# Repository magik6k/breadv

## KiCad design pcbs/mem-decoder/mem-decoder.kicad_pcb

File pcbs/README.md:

## BreadV PCBs

---------
| PCB           | Description                | Status        | Image                          |
|---------------|----------------------------|---------------|--------------------------------|
| ALU           | RiscV ALU                  | Scratch       |                                |
| CSR           | CSR controller             | Scratch       |                                |
| Reg           | 32bit register             | Scratch       |                                |
| ucode breaker | ucode eeprom breakout      | Scratch       |                                |
| Power         | Voltage regulator breakout | Done / In-use |                                |
| 8view         | 8bit bus bin/hex viewer    | Done / In-use |  |
| 8view-out     | 8view ffc breakout         | Done / In-use |                                |

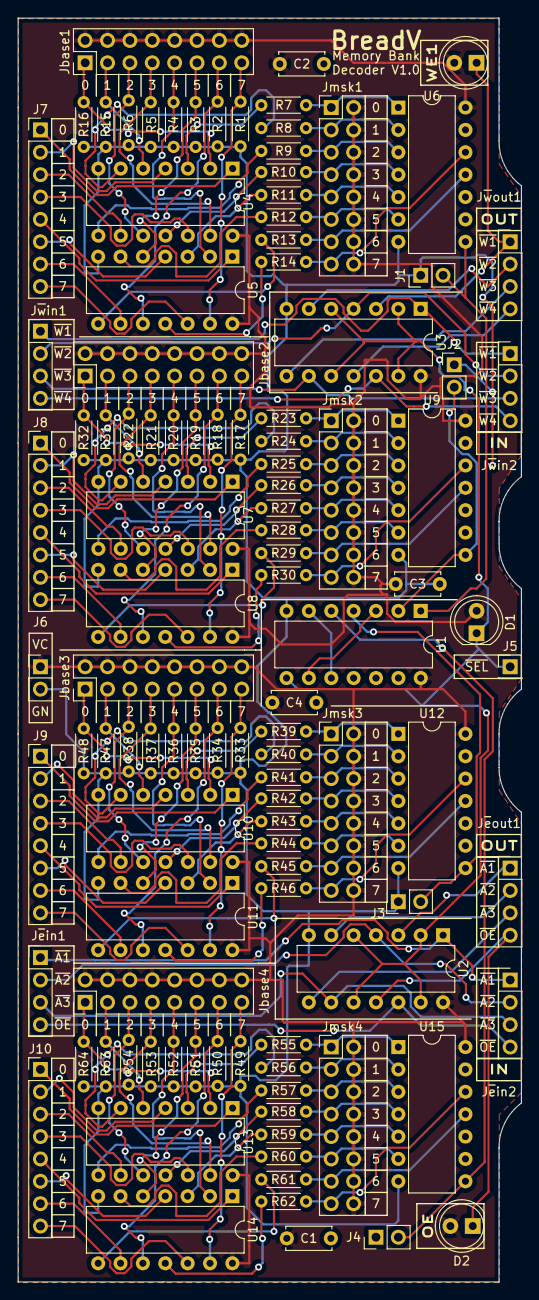
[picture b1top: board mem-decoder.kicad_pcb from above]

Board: 2 copper layers, 57.1 x 143.5 mm, 110 parts (0 on the bottom side), 153 nets.

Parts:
C1, C2, C3, C4: C; C_Disc_D5.0mm_W2.5mm_P5.00mm
D1, D2, D3: LED; LED_D5.0mm
J1, J2, J3, J4, J6: Conn_01x02_Male; PinHeader_1x02_P2.54mm_Vertical
J5: Conn_01x01_Male; PinHeader_1x01_P2.54mm_Vertical
J7, J8, J9, J10: Conn_01x08_Female; PinHeader_1x08_P2.54mm_Vertical
Jbase1, Jbase2, Jbase3, Jbase4: Conn_02x08_Odd_Even; PinHeader_2x08_P2.54mm_Vertical
Jmsk1, Jmsk2, Jmsk3, Jmsk4: Conn_02x08_Odd_Even; PinHeader_2x08_P2.54mm_Vertical
J~{e}in1, J~{e}in2: Conn_01x04_Male; PinHeader_1x04_P2.54mm_Vertical
J~{e}out1: Conn_01x04_Male; PinHeader_1x04_P2.54mm_Vertical
J~{w}in1, J~{w}in2: Conn_01x04_Male; PinHeader_1x04_P2.54mm_Vertical
J~{w}out1: Conn_01x04_Male; PinHeader_1x04_P2.54mm_Vertical
R1, R2, R3, R4, R5, R6, R7, R8, R9, R10, R11, R12, R13, R14, R15, R16, R17, R18, R19, R20, R21, R22, R23, R24, R25, R26, R27, R28, R29, R30, R31, R32, R33, R34, R35, R36, R37, R38, R39, R40, R41, R42, R43, R44, R45, R46, R47, R48, R49, R50, R51, R52, R53, R54, R55, R56, R57, R58, R59, R60, R61, R62, R63, R64: 1K; R_Axial_DIN0204_L3.6mm_D1.6mm_P5.08mm_Horizontal
U1, U2, U3: 74LS32; DIP-14_W7.62mm
U4, U5, U7, U8, U10, U11, U13, U14: 74LS08; DIP-14_W7.62mm
U6, U9, U12, U15: 74LS30; DIP-14_W7.62mm

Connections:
+5V: C1.1, C2.1, C3.1, C4.1, D1.2 (A), D2.2 (A), D3.2 (A), J6.1, Jbase1.2, Jbase1.4, Jbase1.6, Jbase1.8, Jbase1.10, Jbase1.12, Jbase1.14, Jbase1.16, Jbase2.2, Jbase2.4, Jbase2.6, Jbase2.8, Jbase2.10, Jbase2.12, Jbase2.14, Jbase2.16, Jbase3.2, Jbase3.4, Jbase3.6, Jbase3.8, Jbase3.10, Jbase3.12, Jbase3.14, Jbase3.16, Jbase4.2, Jbase4.4, Jbase4.6, Jbase4.8, Jbase4.10, Jbase4.12, Jbase4.14, Jbase4.16, Jmsk1.2, Jmsk1.4, Jmsk1.6, Jmsk1.8, Jmsk1.10, Jmsk1.12, Jmsk1.14, Jmsk1.16, Jmsk2.2, Jmsk2.4, Jmsk2.6, Jmsk2.8, Jmsk2.10, Jmsk2.12, Jmsk2.14, Jmsk2.16, Jmsk3.2, Jmsk3.4, Jmsk3.6, Jmsk3.8, Jmsk3.10, Jmsk3.12, Jmsk3.14, Jmsk3.16, Jmsk4.2, Jmsk4.4, Jmsk4.6, Jmsk4.8, Jmsk4.10, Jmsk4.12, Jmsk4.14, Jmsk4.16, U1.14 (VCC), U2.14 (VCC), U3.14 (VCC), U4.14 (VCC), U5.14 (VCC), U6.14 (VCC), U7.14 (VCC), U8.14 (VCC), U9.14 (VCC), U10.14 (VCC), U11.14 (VCC), U12.14 (VCC), U13.14 (VCC), U14.14 (VCC), U15.14 (VCC)
/8bitmask1/A1: J8.1, U7.1
/8bitmask1/A2: J8.2, U7.4
/8bitmask1/A3: J8.3, U7.9
/8bitmask1/A4: J8.4, U7.12
/8bitmask1/A5: J8.5, U8.1
/8bitmask1/A6: J8.6, U8.4
/8bitmask1/A7: J8.7, U8.9
/8bitmask1/A8: J8.8, U8.12
/8bitmask1/B1: Jbase2.1, R32.2, U7.2
/8bitmask1/B2: Jbase2.3, R31.2, U7.5
/8bitmask1/B3: Jbase2.5, R22.2, U7.10
/8bitmask1/B4: Jbase2.7, R21.2, U7.13
/8bitmask1/B5: Jbase2.9, R20.2, U8.2
/8bitmask1/B6: Jbase2.11, R19.2, U8.5
/8bitmask1/B7: Jbase2.13, R18.2, U8.10
/8bitmask1/B8: Jbase2.15, R17.2, U8.13
/8bitmask1/M1: Jmsk2.1, R23.2, U9.1
/8bitmask1/M2: Jmsk2.3, R24.2, U9.2
/8bitmask1/M3: Jmsk2.5, R25.2, U9.3
/8bitmask1/M4: Jmsk2.7, R26.2, U9.4
/8bitmask1/M5: Jmsk2.9, R27.2, U9.5
/8bitmask1/M6: Jmsk2.11, R28.2, U9.6
/8bitmask1/M7: Jmsk2.13, R29.2, U9.11
/8bitmask1/M8: Jmsk2.15, R30.2, U9.12
/8bitmask1/O: J2.2, U1.2, U9.8
/8bitmask2/A1: J9.1, U10.1
/8bitmask2/A2: J9.2, U10.4
/8bitmask2/A3: J9.3, U10.9
/8bitmask2/A4: J9.4, U10.12
/8bitmask2/A5: J9.5, U11.1
/8bitmask2/A6: J9.6, U11.4
/8bitmask2/A7: J9.7, U11.9
/8bitmask2/A8: J9.8, U11.12
/8bitmask2/B1: Jbase3.1, R48.2, U10.2
/8bitmask2/B2: Jbase3.3, R47.2, U10.5
/8bitmask2/B3: Jbase3.5, R38.2, U10.10
/8bitmask2/B4: Jbase3.7, R37.2, U10.13
/8bitmask2/B5: Jbase3.9, R36.2, U11.2
/8bitmask2/B6: Jbase3.11, R35.2, U11.5
/8bitmask2/B7: Jbase3.13, R34.2, U11.10
/8bitmask2/B8: Jbase3.15, R33.2, U11.13
/8bitmask2/M1: Jmsk3.1, R39.2, U12.1
/8bitmask2/M2: Jmsk3.3, R40.2, U12.2
/8bitmask2/M3: Jmsk3.5, R41.2, U12.3
/8bitmask2/M4: Jmsk3.7, R42.2, U12.4
/8bitmask2/M5: Jmsk3.9, R43.2, U12.5
/8bitmask2/M6: Jmsk3.11, R44.2, U12.6
/8bitmask2/M7: Jmsk3.13, R45.2, U12.11
/8bitmask2/M8: Jmsk3.15, R46.2, U12.12
/8bitmask2/O: J3.2, U1.4, U12.8
/8bitmask3/A1: J10.1, U13.1
/8bitmask3/A2: J10.2, U13.4
/8bitmask3/A3: J10.3, U13.9
/8bitmask3/A4: J10.4, U13.12
/8bitmask3/A5: J10.5, U14.1
/8bitmask3/A6: J10.6, U14.4
/8bitmask3/A7: J10.7, U14.9
/8bitmask3/A8: J10.8, U14.12
/8bitmask3/B1: Jbase4.1, R64.2, U13.2
/8bitmask3/B2: Jbase4.3, R63.2, U13.5
/8bitmask3/B3: Jbase4.5, R54.2, U13.10
/8bitmask3/B4: Jbase4.7, R53.2, U13.13
/8bitmask3/B5: Jbase4.9, R52.2, U14.2
/8bitmask3/B6: Jbase4.11, R51.2, U14.5
/8bitmask3/B7: Jbase4.13, R50.2, U14.10
/8bitmask3/B8: Jbase4.15, R49.2, U14.13
/8bitmask3/M1: Jmsk4.1, R55.2, U15.1
/8bitmask3/M2: Jmsk4.3, R56.2, U15.2
/8bitmask3/M3: Jmsk4.5, R57.2, U15.3
/8bitmask3/M4: Jmsk4.7, R58.2, U15.4
/8bitmask3/M5: Jmsk4.9, R59.2, U15.5
/8bitmask3/M6: Jmsk4.11, R60.2, U15.6
/8bitmask3/M7: Jmsk4.13, R61.2, U15.11
/8bitmask3/M8: Jmsk4.15, R62.2, U15.12
/8bitmask3/O: J4.2, U1.5, U15.8
/8bitmask/A1: J7.1, U4.1
/8bitmask/A2: J7.2, U4.4
/8bitmask/A3: J7.3, U4.9
/8bitmask/A4: J7.4, U4.12
/8bitmask/A5: J7.5, U5.1
/8bitmask/A6: J7.6, U5.4
/8bitmask/A7: J7.7, U5.9
/8bitmask/A8: J7.8, U5.12
/8bitmask/B1: Jbase1.1, R16.2, U4.2
/8bitmask/B2: Jbase1.3, R15.2, U4.5
/8bitmask/B3: Jbase1.5, R6.2, U4.10
/8bitmask/B4: Jbase1.7, R5.2, U4.13
/8bitmask/B5: Jbase1.9, R4.2, U5.2
/8bitmask/B6: Jbase1.11, R3.2, U5.5
/8bitmask/B7: Jbase1.13, R2.2, U5.10
/8bitmask/B8: Jbase1.15, R1.2, U5.13
/8bitmask/M1: Jmsk1.1, R7.2, U6.1
/8bitmask/M2: Jmsk1.3, R8.2, U6.2
/8bitmask/M3: Jmsk1.5, R9.2, U6.3
/8bitmask/M4: Jmsk1.7, R10.2, U6.4
/8bitmask/M5: Jmsk1.9, R11.2, U6.5
/8bitmask/M6: Jmsk1.11, R12.2, U6.6
/8bitmask/M7: Jmsk1.13, R13.2, U6.11
/8bitmask/M8: Jmsk1.15, R14.2, U6.12
/8bitmask/O: J1.2, U1.1, U6.8
/~sel: D1.1 (K), J5.1, U1.8, U2.2, U2.5, U2.10, U2.13, U3.2, U3.5, U3.10, U3.13
GND: C1.2, C2.2, C3.2, C4.2, J1.1, J2.1, J3.1, J4.1, J6.2, R1.1, R2.1, R3.1, R4.1, R5.1, R6.1, R15.1, R16.1, R17.1, R18.1, R19.1, R20.1, R21.1, R22.1, R31.1, R32.1, R33.1, R34.1, R35.1, R36.1, R37.1, R38.1, R47.1, R48.1, R49.1, R50.1, R51.1, R52.1, R53.1, R54.1, R63.1, R64.1, U1.7 (GND), U2.7 (GND), U3.7 (GND), U4.7 (GND), U5.7 (GND), U6.7 (GND), U7.7 (GND), U8.7 (GND), U9.7 (GND), U10.7 (GND), U11.7 (GND), U12.7 (GND), U13.7 (GND), U14.7 (GND), U15.7 (GND)
unnamed: R7.1, U4.3
unnamed: R8.1, U4.6
unnamed: R9.1, U4.8
unnamed: R10.1, U4.11
unnamed: R11.1, U5.3
unnamed: R12.1, U5.6
unnamed: R13.1, U5.8
unnamed: R14.1, U5.11
unnamed: R23.1, U7.3
unnamed: R24.1, U7.6
unnamed: R25.1, U7.8
unnamed: R26.1, U7.11
unnamed: R27.1, U8.3
unnamed: R28.1, U8.6
unnamed: R29.1, U8.8
unnamed: R30.1, U8.11
unnamed: R39.1, U10.3
unnamed: R40.1, U10.6
unnamed: R41.1, U10.8
unnamed: R42.1, U10.11
unnamed: R43.1, U11.3
unnamed: R44.1, U11.6
unnamed: R45.1, U11.8
unnamed: R46.1, U11.11
unnamed: R55.1, U13.3
unnamed: R56.1, U13.6
unnamed: R57.1, U13.8
unnamed: R58.1, U13.11
unnamed: R59.1, U14.3
unnamed: R60.1, U14.6
unnamed: R61.1, U14.8
unnamed: R62.1, U14.11
unnamed: U1.3, U1.9
unnamed: U1.6, U1.10
~Laux1o: J~{e}out1.1, U2.3
~Laux1: J~{e}in1.1, J~{e}in2.1, U2.1
~Laux2o: J~{e}out1.2, U2.6
~Laux2: J~{e}in1.2, J~{e}in2.2, U2.4
~Laux3o: J~{e}out1.3, U2.8
~Laux3: J~{e}in1.3, J~{e}in2.3, U2.9
~OEin: J~{e}in1.4, J~{e}in2.4, U2.12
~OEout: D2.1 (K), J~{e}out1.4, U2.11
~WEin1: J~{w}in1.1, J~{w}in2.1, U3.1
~WEin2: J~{w}in1.2, J~{w}in2.2, U3.4
~WEin3: J~{w}in1.3, J~{w}in2.3, U3.9
~WEin4: J~{w}in1.4, J~{w}in2.4, U3.12
~WEout1: D3.1 (K), J~{w}out1.1, U3.3
~WEout2: J~{w}out1.2, U3.6
~WEout3: J~{w}out1.3, U3.8
~WEout4: J~{w}out1.4, U3.11

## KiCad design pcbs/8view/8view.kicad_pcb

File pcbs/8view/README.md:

## 8view

8bit bus bin/hex viewer

### Features
* 8 LEDs viewing bits
* 2 7-segment displays for hex driven by attiny828 used mostly as LUT

### Flashing

```
$ avr-gcc -mmcu=attiny828 8view.c -Os -o 8view.o && avr-objcopy -j .text -j .data -O ihex 8view.o 8view.hex

# Works with arduino isp
$ avrdude -p t828 -P /dev/ttyXX -c avrisp -b 19200 -U flash:w:8view.hex -F
```

### TODO
* Make high-impedance
* Implement snapshot / record mode

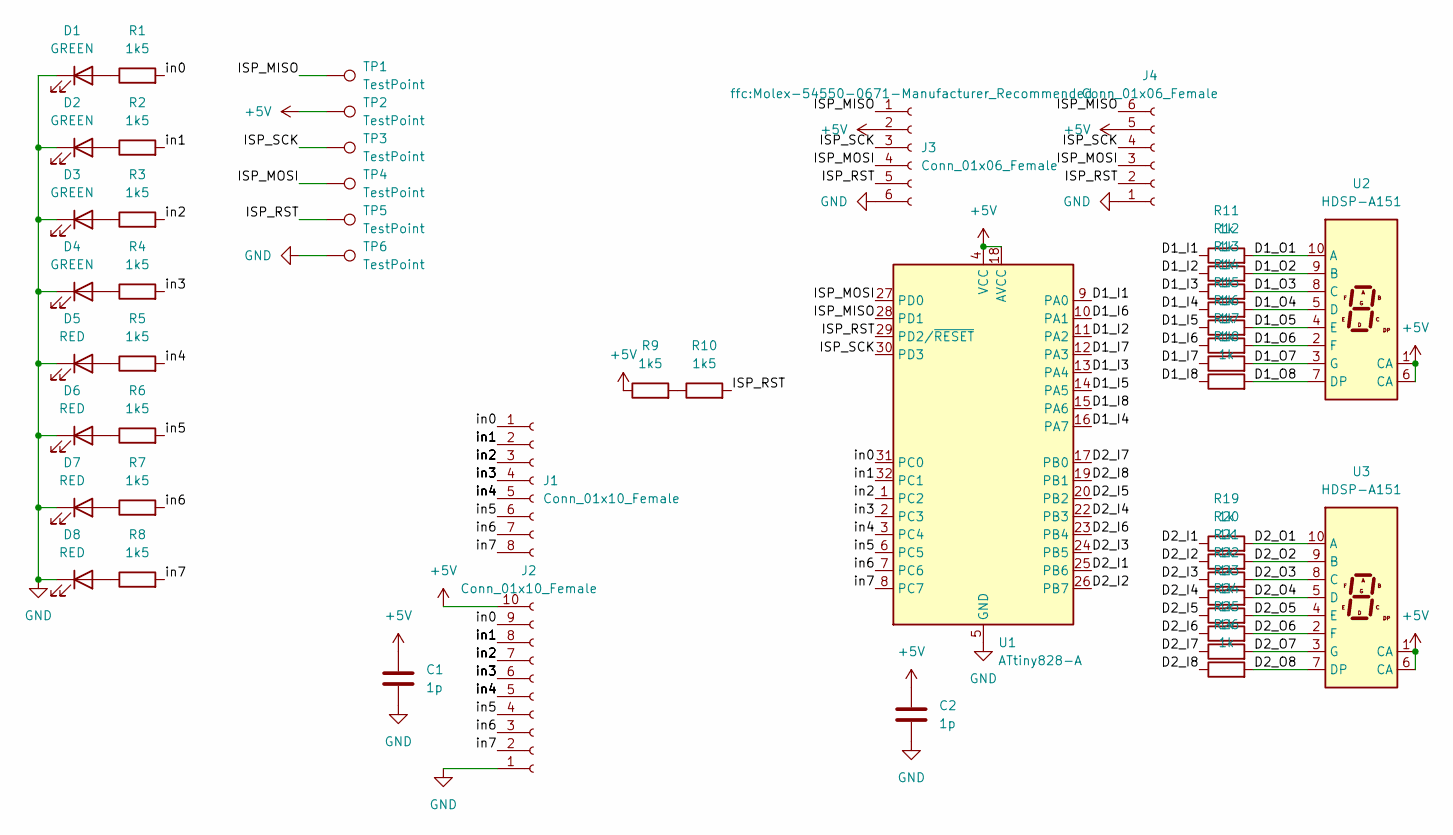
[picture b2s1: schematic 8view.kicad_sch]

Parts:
C1, C2: 1p; C_0603_1608Metric
D1, D2, D3, D4: GREEN; LED_0603_1608Metric
D5, D6, D7, D8: RED; LED_0603_1608Metric
J1: Conn_01x10_Female; PinHeader_1x08_P2.54mm_Horizontal
J2: Conn_01x10_Female; PinHeader_1x10_P2.54mm_Horizontal
J3, J4: Conn_01x06_Female; Molex-54550-0671-Manufacturer_Recommended
R1, R2, R3, R4, R5, R6, R7, R8, R9, R10: 1k5; R_0402_1005Metric
R11, R12, R13, R14, R15, R16, R17, R18, R19, R20, R21, R22, R23, R24, R25, R26: 1k; R_0402_1005Metric
TP1, TP2, TP3, TP4, TP5, TP6: TestPoint; TestPoint_Pad_D1.5mm
U1: ATtiny828-A; TQFP-32_7x7mm_P0.8mm
U2, U3: HDSP-A151

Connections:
+5V: C1.1, C2.1, J2.10, J3.2, J4.5, R9.1, TP2.1, U1.4 (VCC), U1.18 (AVCC), U2.1 (CA), U2.6 (CA), U3.1 (CA), U3.6 (CA)
/D1_I1: R11.1, U1.9 (PA0)
/D1_I2: R12.1, U1.11 (PA2)
/D1_I3: R13.1, U1.13 (PA4)
/D1_I4: R14.1, U1.16 (PA7)
/D1_I5: R15.1, U1.14 (PA5)
/D1_I6: R16.1, U1.10 (PA1)
/D1_I7: R17.1, U1.12 (PA3)
/D1_I8: R18.1, U1.15 (PA6)
/D1_O1: R11.2, U2.10 (A)
/D1_O2: R12.2, U2.9 (B)
/D1_O3: R13.2, U2.8 (C)
/D1_O4: R14.2, U2.5 (D)
/D1_O5: R15.2, U2.4 (E)
/D1_O6: R16.2, U2.2 (F)
/D1_O7: R17.2, U2.3 (G)
/D1_O8: R18.2, U2.7 (DP)
/D2_I1: R19.1, U1.25 (PB6)
/D2_I2: R20.1, U1.26 (PB7)
/D2_I3: R21.1, U1.24 (PB5)
/D2_I4: R22.1, U1.22 (PB3)
/D2_I5: R23.1, U1.20 (PB2)
/D2_I6: R24.1, U1.23 (PB4)
/D2_I7: R25.1, U1.17 (PB0)
/D2_I8: R26.1, U1.19 (PB1)
/D2_O1: R19.2, U3.10 (A)
/D2_O2: R20.2, U3.9 (B)
/D2_O3: R21.2, U3.8 (C)
/D2_O4: R22.2, U3.5 (D)
/D2_O5: R23.2, U3.4 (E)
/D2_O6: R24.2, U3.2 (F)
/D2_O7: R25.2, U3.3 (G)
/D2_O8: R26.2, U3.7 (DP)
/ISP_MISO: J3.1, J4.6, TP1.1, U1.28 (PD1)
/ISP_MOSI: J3.4, J4.3, TP4.1, U1.27 (PD0)
/ISP_RST: J3.5, J4.2, R10.2, TP5.1, U1.29 (PD2/~RESET)
/ISP_SCK: J3.3, J4.4, TP3.1, U1.30 (PD3)
/in0: J1.1, J2.9, R1.2, U1.31 (PC0)
/in1: J1.2, J2.8, R2.2, U1.32 (PC1)
/in2: J1.3, J2.7, R3.2, U1.1 (PC2)
/in3: J1.4, J2.6, R4.2, U1.2 (PC3)
/in4: J1.5, J2.5, R5.2, U1.3 (PC4)
/in5: J1.6, J2.4, R6.2, U1.6 (PC5)
/in6: J1.7, J2.3, R7.2, U1.7 (PC6)
/in7: J1.8, J2.2, R8.2, U1.8 (PC7)
GND: C1.2, C2.2, D1.1 (K), D2.1 (K), D3.1 (K), D4.1 (K), D5.1 (K), D6.1 (K), D7.1 (K), D8.1 (K), J2.1, J3.6, J4.1, TP6.1, U1.5 (GND), U1.21 (GND)
unnamed: D1.2 (A), R1.1
unnamed: D2.2 (A), R2.1
unnamed: D3.2 (A), R3.1
unnamed: D4.2 (A), R4.1
unnamed: D5.2 (A), R5.1
unnamed: D6.2 (A), R6.1
unnamed: D7.2 (A), R7.1
unnamed: D8.2 (A), R8.1
unnamed: R9.2, R10.1

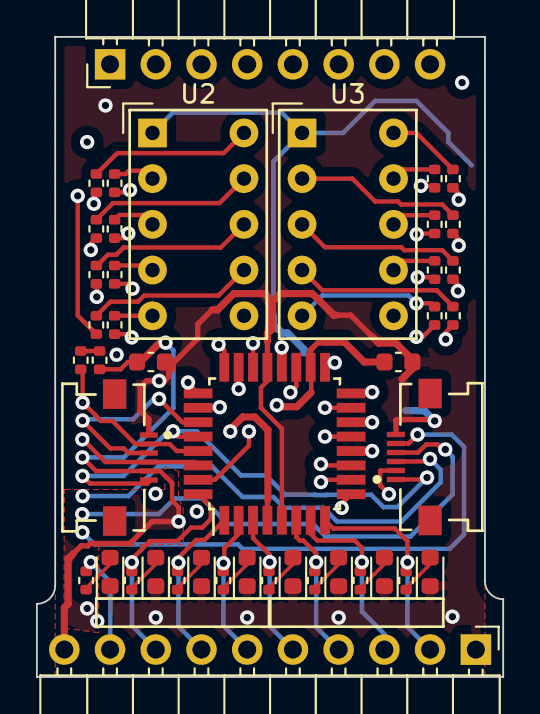
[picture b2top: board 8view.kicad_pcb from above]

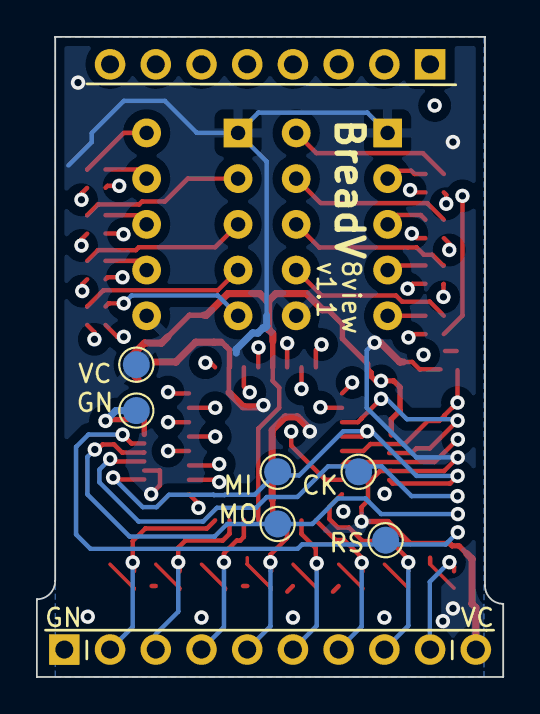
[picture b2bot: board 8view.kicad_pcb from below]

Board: 4 copper layers, 25.9 x 35.6 mm, 49 parts (6 on the bottom side), 55 nets.

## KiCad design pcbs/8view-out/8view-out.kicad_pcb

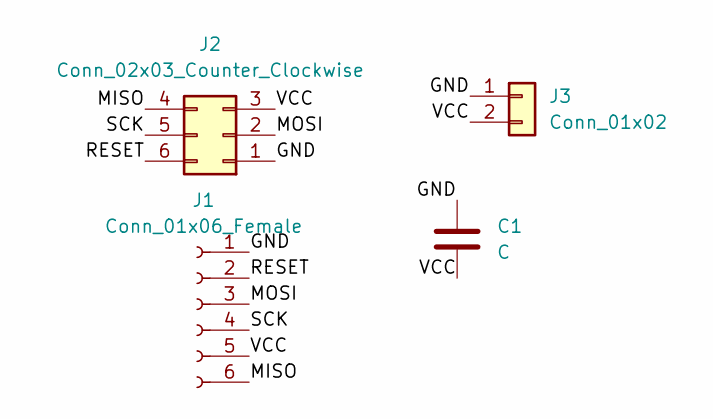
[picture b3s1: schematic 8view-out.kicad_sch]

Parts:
C1: C
J1: Conn_01x06_Female; Molex-54550-0671-Manufacturer_Recommended
J2: Conn_02x03_Counter_Clockwise; PinHeader_2x03_P2.54mm_Vertical
J3: Conn_01x02

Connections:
/GND: C1.1, J1.1, J2.1, J3.1
/MISO: J1.6, J2.4
/MOSI: J1.3, J2.2
/RESET: J1.2, J2.6
/SCK: J1.4, J2.5
/VCC: C1.2, J1.5, J2.3, J3.2

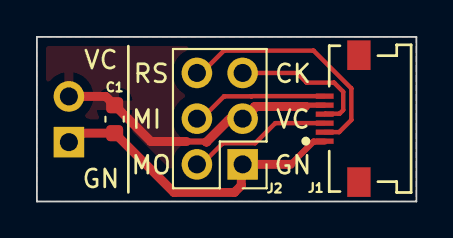
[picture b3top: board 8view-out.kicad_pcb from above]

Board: 2 copper layers, 21.1 x 9.1 mm, 4 parts (1 on the bottom side), 6 nets.

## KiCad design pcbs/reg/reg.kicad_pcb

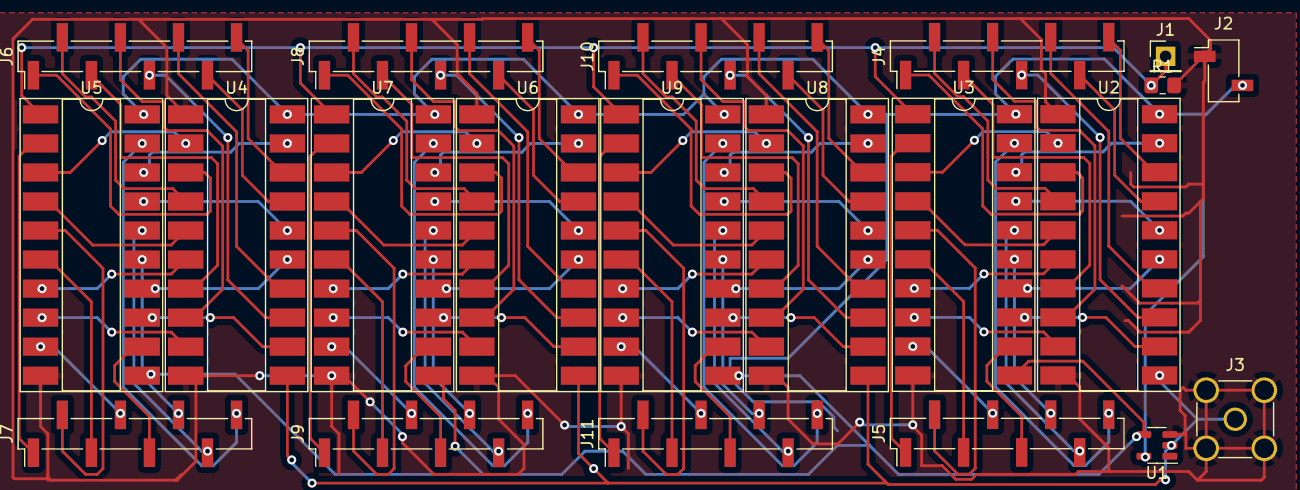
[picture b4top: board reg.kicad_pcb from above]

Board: 2 copper layers, 21 parts (0 on the bottom side), 101 nets.

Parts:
J1: Conn_01x01_Female; PinHeader_1x01_P2.54mm_Vertical
J2: Conn_01x02_Male; PinSocket_1x02_P2.54mm_Vertical_SMD_Pin1Left
J3: Conn_Coaxial; SMA_Amphenol_901-144_Vertical
J4, J5, J6, J7, J8, J9, J10, J11: Conn_01x08; PinHeader_1x08_P2.54mm_Vertical_SMD_Pin1Left
R1: R; R_0805_2012Metric_Pad1.20x1.40mm_HandSolder
U1: SN74LVC1G14DBV; SOT-23-5
U2, U3, U4, U5, U6, U7, U8, U9: 74LS377; DIP-20_W8.89mm_SMDSocket_LongPads

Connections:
+5V: J2.2, U1.5 (VCC), U2.20 (VCC), U3.20 (VCC), U4.20 (VCC), U5.20 (VCC), U6.20 (VCC), U7.20 (VCC), U8.20 (VCC), U9.20 (VCC)
/CLK: J3.1 (In), U1.2, U2.11 (CP), U4.11 (CP), U6.11 (CP), U8.11 (CP)
/~CLK: U1.4, U3.11 (CP), U5.11 (CP), U7.11 (CP), U9.11 (CP)
/~E: J1.1, R1.1, U3.1 (~E), U5.1 (~E), U7.1 (~E), U9.1 (~E)
GND: J2.1, J3.2 (Ext), R1.2, U1.3 (GND), U2.1 (~E), U2.10 (GND), U3.10 (GND), U4.1 (~E), U4.10 (GND), U5.10 (GND), U6.1 (~E), U6.10 (GND), U7.10 (GND), U8.1 (~E), U8.10 (GND), U9.10 (GND)
unnamed: J4.1, U2.3 (D0)
unnamed: J4.2, U2.4 (D1)
unnamed: J4.3, U2.7 (D2)
unnamed: J4.4, U2.8 (D3)
unnamed: J4.5, U2.13 (D4)
unnamed: J4.6, U2.14 (D5)
unnamed: J4.7, U2.17 (D6)
unnamed: J4.8, U2.18 (D7)
unnamed: J5.1, U3.2 (Q0)
unnamed: J5.2, U3.5 (Q1)
unnamed: J5.3, U3.6 (Q2)
unnamed: J5.4, U3.9 (Q3)
unnamed: J5.5, U3.12 (Q4)
unnamed: J5.6, U3.15 (Q5)
unnamed: J5.7, U3.16 (Q6)
unnamed: J5.8, U3.19 (Q7)
unnamed: J6.1, U4.3 (D0)
unnamed: J6.2, U4.4 (D1)
unnamed: J6.3, U4.7 (D2)
unnamed: J6.4, U4.8 (D3)
unnamed: J6.5, U4.13 (D4)
unnamed: J6.6, U4.14 (D5)
unnamed: J6.7, U4.17 (D6)
unnamed: J6.8, U4.18 (D7)
unnamed: J7.1, U5.2 (Q0)
unnamed: J7.2, U5.5 (Q1)
unnamed: J7.3, U5.6 (Q2)
unnamed: J7.4, U5.9 (Q3)
unnamed: J7.5, U5.12 (Q4)
unnamed: J7.6, U5.15 (Q5)
unnamed: J7.7, U5.16 (Q6)
unnamed: J7.8, U5.19 (Q7)
unnamed: J8.1, U6.3 (D0)
unnamed: J8.2, U6.4 (D1)
unnamed: J8.3, U6.7 (D2)
unnamed: J8.4, U6.8 (D3)
unnamed: J8.5, U6.13 (D4)
unnamed: J8.6, U6.14 (D5)
unnamed: J8.7, U6.17 (D6)
unnamed: J8.8, U6.18 (D7)
unnamed: J9.1, U7.2 (Q0)
unnamed: J9.2, U7.5 (Q1)
unnamed: J9.3, U7.6 (Q2)
unnamed: J9.4, U7.9 (Q3)
unnamed: J9.5, U7.12 (Q4)
unnamed: J9.6, U7.15 (Q5)
unnamed: J9.7, U7.16 (Q6)
unnamed: J9.8, U7.19 (Q7)
unnamed: J10.1, U8.3 (D0)
unnamed: J10.2, U8.4 (D1)
unnamed: J10.3, U8.7 (D2)
unnamed: J10.4, U8.8 (D3)
unnamed: J10.5, U8.13 (D4)
unnamed: J10.6, U8.14 (D5)
unnamed: J10.7, U8.17 (D6)
unnamed: J10.8, U8.18 (D7)
unnamed: J11.1, U9.2 (Q0)
unnamed: J11.2, U9.5 (Q1)
unnamed: J11.3, U9.6 (Q2)
unnamed: J11.4, U9.9 (Q3)
unnamed: J11.5, U9.12 (Q4)
unnamed: J11.6, U9.15 (Q5)
unnamed: J11.7, U9.16 (Q6)
unnamed: J11.8, U9.19 (Q7)
unnamed: U2.2 (Q0), U3.3 (D0)
unnamed: U2.5 (Q1), U3.4 (D1)
unnamed: U2.6 (Q2), U3.7 (D2)
unnamed: U2.9 (Q3), U3.8 (D3)
unnamed: U2.12 (Q4), U3.13 (D4)
unnamed: U2.15 (Q5), U3.14 (D5)
unnamed: U2.16 (Q6), U3.17 (D6)
unnamed: U2.19 (Q7), U3.18 (D7)
unnamed: U4.2 (Q0), U5.3 (D0)
unnamed: U4.5 (Q1), U5.4 (D1)
unnamed: U4.6 (Q2), U5.7 (D2)
unnamed: U4.9 (Q3), U5.8 (D3)
unnamed: U4.12 (Q4), U5.13 (D4)
unnamed: U4.15 (Q5), U5.14 (D5)
unnamed: U4.16 (Q6), U5.17 (D6)
unnamed: U4.19 (Q7), U5.18 (D7)
unnamed: U6.2 (Q0), U7.3 (D0)
unnamed: U6.5 (Q1), U7.4 (D1)
unnamed: U6.6 (Q2), U7.7 (D2)
unnamed: U6.9 (Q3), U7.8 (D3)
unnamed: U6.12 (Q4), U7.13 (D4)
unnamed: U6.15 (Q5), U7.14 (D5)
unnamed: U6.16 (Q6), U7.17 (D6)
unnamed: U6.19 (Q7), U7.18 (D7)
unnamed: U8.2 (Q0), U9.3 (D0)
unnamed: U8.5 (Q1), U9.4 (D1)
unnamed: U8.6 (Q2), U9.7 (D2)
unnamed: U8.9 (Q3), U9.8 (D3)
unnamed: U8.12 (Q4), U9.13 (D4)
unnamed: U8.15 (Q5), U9.14 (D5)
unnamed: U8.16 (Q6), U9.17 (D6)
unnamed: U8.19 (Q7), U9.18 (D7)

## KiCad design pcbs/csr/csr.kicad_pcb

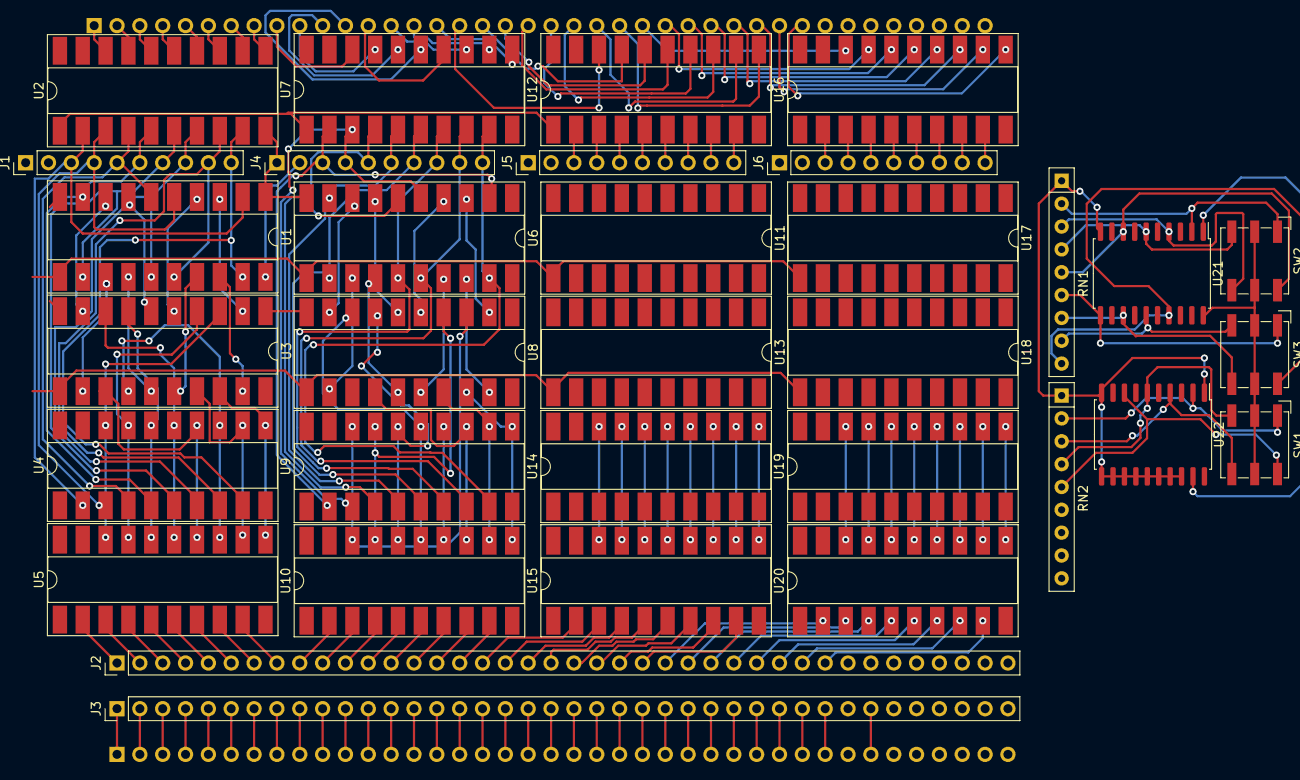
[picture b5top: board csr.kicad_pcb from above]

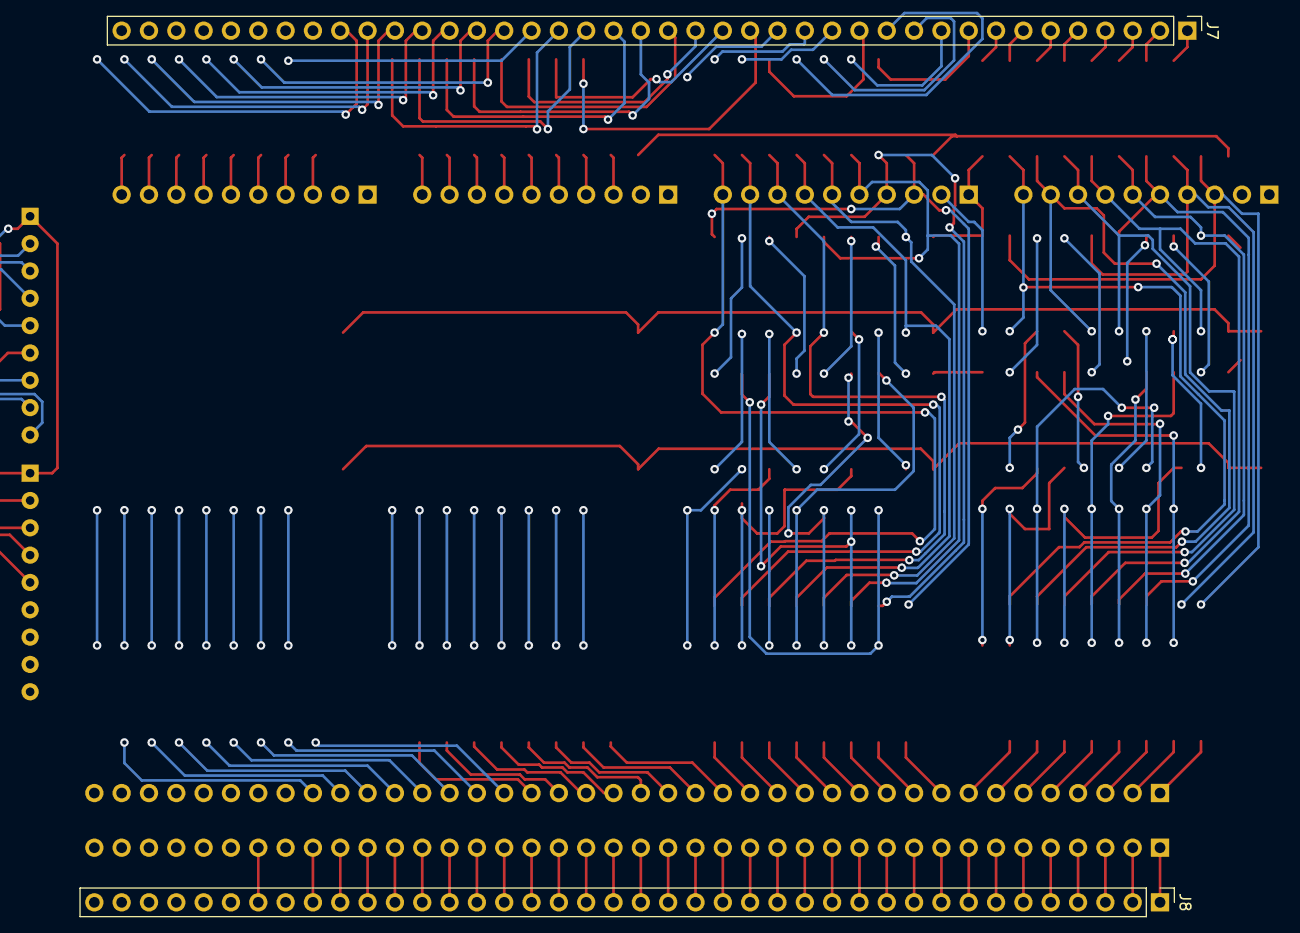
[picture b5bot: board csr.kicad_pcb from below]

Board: 2 copper layers, 35 parts (2 on the bottom side), 214 nets.

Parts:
J1, J4, J5, J6: Conn_01x10_Female; PinHeader_1x10_P2.54mm_Vertical
J2, J3: Conn_01x40_Female; PinHeader_1x40_P2.54mm_Vertical
J7, J8: Conn_01x40_Male; PinHeader_1x40_P2.54mm_Vertical
RN1, RN2: R_Network08; R_Array_SIP9
SW1, SW2, SW3: SW_Coded_SH-7050; Nidec_Copal_SH-7010A
U1, U3, U6, U8, U11, U13, U17, U18: 74LS377; DIP-20_W8.89mm_SMDSocket_LongPads
U2, U4, U5, U7, U9, U10, U12, U14, U15, U16, U19, U20: 74HCT541; DIP-20_W8.89mm_SMDSocket_LongPads
U21, U22: 74HC688; SOIC-20W_7.5x12.8mm_P1.27mm

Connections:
+5V: J1.2, J3.39, J4.2, J5.2, J6.2, SW1.C, SW2.C, SW3.C, U1.20 (VCC), U2.20 (VCC), U3.20 (VCC), U4.20 (VCC), U5.20 (VCC), U6.20 (VCC), U7.20 (VCC), U8.20 (VCC), U9.20 (VCC), U10.20 (VCC), U11.20 (VCC), U12.20 (VCC), U13.20 (VCC), U14.20 (VCC), U15.20 (VCC), U16.20 (VCC), U17.20 (VCC), U18.20 (VCC), U19.20 (VCC), U20.20 (VCC), U21.20 (VCC), U22.20 (VCC)
GND: J1.1, J3.40, J4.1, J5.1, J6.1, RN1.1 (common), RN2.1 (common), U1.1 (~E), U1.10 (GND), U2.10 (GND), U3.1 (~E), U3.10 (GND), U4.1 (G1), U4.10 (GND), U5.1 (G1), U5.10 (GND), U6.1 (~E), U6.10 (GND), U7.10 (GND), U8.1 (~E), U8.10 (GND), U9.1 (G1), U9.10 (GND), U10.1 (G1), U10.10 (GND), U11.1 (~E), U11.10 (GND), U12.10 (GND), U13.1 (~E), U13.10 (GND), U14.1 (G1), U14.10 (GND), U15.1 (G1), U15.10 (GND), U16.10 (GND), U17.1 (~E), U17.10 (GND), U18.1 (~E), U18.10 (GND), U19.1 (G1), U19.10 (GND), U20.1 (G1), U20.10 (GND), U21.10 (GND), U22.1 (G), U22.10 (GND), U22.11 (P4), U22.12 (R4), U22.13 (P5), U22.14 (R5), U22.15 (P6), U22.16 (R6), U22.17 (P7), U22.18 (R7)
unnamed: U1.3 (D0), U3.2 (Q0)
unnamed: U1.4 (D1), U3.5 (Q1)
unnamed: U1.7 (D2), U3.6 (Q2)
unnamed: U1.8 (D3), U3.9 (Q3)
unnamed: U1.13 (D4), U3.12 (Q4)
unnamed: U1.14 (D5), U3.15 (Q5)
unnamed: U1.17 (D6), U3.16 (Q6)
unnamed: U1.18 (D7), U3.19 (Q7)
unnamed: U21.1 (G), U22.19 (P=R)
unnamed: U6.3 (D0), U8.2 (Q0)
unnamed: U6.4 (D1), U8.5 (Q1)
unnamed: U6.7 (D2), U8.6 (Q2)
unnamed: U6.8 (D3), U8.9 (Q3)
unnamed: U6.13 (D4), U8.12 (Q4)
unnamed: U6.14 (D5), U8.15 (Q5)
unnamed: U6.17 (D6), U8.16 (Q6)
unnamed: U6.18 (D7), U8.19 (Q7)
unnamed: U11.3 (D0), U13.2 (Q0)
unnamed: U11.4 (D1), U13.5 (Q1)
unnamed: U11.7 (D2), U13.6 (Q2)
unnamed: U11.8 (D3), U13.9 (Q3)
unnamed: U11.13 (D4), U13.12 (Q4)
unnamed: U11.14 (D5), U13.15 (Q5)
unnamed: U11.17 (D6), U13.16 (Q6)
unnamed: U11.18 (D7), U13.19 (Q7)
unnamed: U17.3 (D0), U18.2 (Q0)
unnamed: U17.4 (D1), U18.5 (Q1)
unnamed: U17.7 (D2), U18.6 (Q2)
unnamed: U17.8 (D3), U18.9 (Q3)
unnamed: U17.13 (D4), U18.12 (Q4)
unnamed: U17.14 (D5), U18.15 (Q5)
unnamed: U17.17 (D6), U18.16 (Q6)
unnamed: U17.18 (D7), U18.19 (Q7)
ca0: RN1.2 (R1), SW2.1, U21.2 (P0)
ca1: RN1.3 (R2), SW2.2, U21.4 (P1)
ca2: RN1.4 (R3), SW2.4, U21.6 (P2)
ca3: RN1.5 (R4), SW2.8, U21.8 (P3)
ca4: RN1.6 (R5), SW3.1, U21.11 (P4)
ca5: RN1.7 (R6), SW3.2, U21.13 (P5)
ca6: RN1.8 (R7), SW3.4, U21.15 (P6)
ca7: RN1.9 (R8), SW3.8, U21.17 (P7)
ca8: RN2.2 (R1), SW1.1, U22.2 (P0)
ca9: RN2.3 (R2), SW1.2, U22.4 (P1)
ca10: RN2.4 (R3), SW1.4, U22.6 (P2)
ca11: RN2.5 (R4), SW1.8, U22.8 (P3)
cin0: J3.1, J8.1
cin1: J3.2, J8.2
cin2: J3.3, J8.3
cin3: J3.4, J8.4
cin4: J3.5, J8.5
cin5: J3.6, J8.6
cin6: J3.7, J8.7
cin7: J3.8, J8.8
cin8: J3.9, J8.9
cin9: J3.10, J8.10
cin10: J3.11, J8.11
cin11: J3.12, J8.12
cin12: J3.13, J8.13
cin13: J3.14, J8.14
cin14: J3.15, J8.15
cin15: J3.16, J8.16
cin16: J3.17, J8.17
cin17: J3.18, J8.18
cin18: J3.19, J8.19
cin19: J3.20, J8.20
cin20: J3.21, J8.21
cin21: J3.22, J8.22
cin22: J3.23, J8.23
cin23: J3.24, J8.24
cin24: J3.25, J8.25
cin25: J3.26, J8.26
cin26: J3.27, J8.27
cin27: J3.28, J8.28
cin28: J3.29, J8.29
cin29: J3.30, J8.30
cin30: J3.31, J8.31
cin31: J3.32, J8.32
clkD: U1.11 (CP), U6.11 (CP), U11.11 (CP), U17.11 (CP)
clkL: U3.11 (CP), U8.11 (CP), U13.11 (CP), U18.11 (CP)
cur0: J1.3, U1.2 (Q0), U2.2 (A0), U4.2 (A0)
cur1: J1.4, U1.5 (Q1), U2.3 (A1), U4.3 (A1)
cur2: J1.5, U1.6 (Q2), U2.4 (A2), U4.4 (A2)
cur3: J1.6, U1.9 (Q3), U2.5 (A3), U4.5 (A3)
cur4: J1.7, U1.12 (Q4), U2.6 (A4), U4.6 (A4)
cur5: J1.8, U1.15 (Q5), U2.7 (A5), U4.7 (A5)
cur6: J1.9, U1.16 (Q6), U2.8 (A6), U4.8 (A6)
cur7: J1.10, U1.19 (Q7), U2.9 (A7), U4.9 (A7)
cur8: J4.3, U6.2 (Q0), U7.2 (A0), U9.2 (A0)
cur9: J4.4, U6.5 (Q1), U7.3 (A1), U9.3 (A1)
cur10: J4.5, U6.6 (Q2), U7.4 (A2), U9.4 (A2)
cur11: J4.6, U6.9 (Q3), U7.5 (A3), U9.5 (A3)
cur12: J4.7, U6.12 (Q4), U7.6 (A4), U9.6 (A4)
cur13: J4.8, U6.15 (Q5), U7.7 (A5), U9.7 (A5)
cur14: J4.9, U6.16 (Q6), U7.8 (A6), U9.8 (A6)
cur15: J4.10, U6.19 (Q7), U7.9 (A7), U9.9 (A7)
cur16: J5.3, U11.2 (Q0), U12.2 (A0), U14.2 (A0)
cur17: J5.4, U11.5 (Q1), U12.3 (A1), U14.3 (A1)
cur18: J5.5, U11.6 (Q2), U12.4 (A2), U14.4 (A2)
cur19: J5.6, U11.9 (Q3), U12.5 (A3), U14.5 (A3)
cur20: J5.7, U11.12 (Q4), U12.6 (A4), U14.6 (A4)
cur21: J5.8, U11.15 (Q5), U12.7 (A5), U14.7 (A5)
cur22: J5.9, U11.16 (Q6), U12.8 (A6), U14.8 (A6)
cur23: J5.10, U11.19 (Q7), U12.9 (A7), U14.9 (A7)
cur24: J6.3, U16.2 (A0), U17.2 (Q0), U19.2 (A0)
cur25: J6.4, U16.3 (A1), U17.5 (Q1), U19.3 (A1)
cur26: J6.5, U16.4 (A2), U17.6 (Q2), U19.4 (A2)
cur27: J6.6, U16.5 (A3), U17.9 (Q3), U19.5 (A3)
cur28: J6.7, U16.6 (A4), U17.12 (Q4), U19.6 (A4)
cur29: J6.8, U16.7 (A5), U17.15 (Q5), U19.7 (A5)
cur30: J6.9, U16.8 (A6), U17.16 (Q6), U19.8 (A6)
cur31: J6.10, U16.9 (A7), U17.19 (Q7), U19.9 (A7)
in0: J2.1, U5.2 (A0)
in1: J2.2, U5.3 (A1)
in2: J2.3, U5.4 (A2)
in3: J2.4, U5.5 (A3)
in4: J2.5, U5.6 (A4)
in5: J2.6, U5.7 (A5)
in6: J2.7, U5.8 (A6)
in7: J2.8, U5.9 (A7)
in8: J2.9, U10.2 (A0)
in9: J2.10, U10.3 (A1)
in10: J2.11, U10.4 (A2)
in11: J2.12, U10.5 (A3)
in12: J2.13, U10.6 (A4)
in13: J2.14, U10.7 (A5)
in14: J2.15, U10.8 (A6)
in15: J2.16, U10.9 (A7)
in16: J2.17, U15.2 (A0)
in17: J2.18, U15.3 (A1)
in18: J2.19, U15.4 (A2)
in19: J2.20, U15.5 (A3)
in20: J2.21, U15.6 (A4)
in21: J2.22, U15.7 (A5)
in22: J2.23, U15.8 (A6)
in23: J2.24, U15.9 (A7)
in24: J2.25, U20.2 (A0)
in25: J2.26, U20.3 (A1)
in26: J2.27, U20.4 (A2)
in27: J2.28, U20.5 (A3)
in28: J2.29, U20.6 (A4)
in29: J2.30, U20.7 (A5)
in30: J2.31, U20.8 (A6)
in31: J2.32, U20.9 (A7)
next0: U3.3 (D0), U4.18 (Y0), U5.18 (Y0)
next1: U3.4 (D1), U4.17 (Y1), U5.17 (Y1)
next2: U3.7 (D2), U4.16 (Y2), U5.16 (Y2)
next3: U3.8 (D3), U4.15 (Y3), U5.15 (Y3)
next4: U3.13 (D4), U4.14 (Y4), U5.14 (Y4)
next5: U3.14 (D5), U4.13 (Y5), U5.13 (Y5)
next6: U3.17 (D6), U4.12 (Y6), U5.12 (Y6)
next7: U3.18 (D7), U4.11 (Y7), U5.11 (Y7)
next8: U8.3 (D0), U9.18 (Y0), U10.18 (Y0)
next9: U8.4 (D1), U9.17 (Y1), U10.17 (Y1)
next10: U8.7 (D2), U9.16 (Y2), U10.16 (Y2)
next11: U8.8 (D3), U9.15 (Y3), U10.15 (Y3)
next12: U8.13 (D4), U9.14 (Y4), U10.14 (Y4)
next13: U8.14 (D5), U9.13 (Y5), U10.13 (Y5)
next14: U8.17 (D6), U9.12 (Y6), U10.12 (Y6)
next15: U8.18 (D7), U9.11 (Y7), U10.11 (Y7)
next16: U13.3 (D0), U14.18 (Y0), U15.18 (Y0)
next17: U13.4 (D1), U14.17 (Y1), U15.17 (Y1)
next18: U13.7 (D2), U14.16 (Y2), U15.16 (Y2)
next19: U13.8 (D3), U14.15 (Y3), U15.15 (Y3)
next20: U13.13 (D4), U14.14 (Y4), U15.14 (Y4)
next21: U13.14 (D5), U14.13 (Y5), U15.13 (Y5)
next22: U13.17 (D6), U14.12 (Y6), U15.12 (Y6)
next23: U13.18 (D7), U14.11 (Y7), U15.11 (Y7)
next24: U18.3 (D0), U19.18 (Y0), U20.18 (Y0)
next25: U18.4 (D1), U19.17 (Y1), U20.17 (Y1)
next26: U18.7 (D2), U19.16 (Y2), U20.16 (Y2)
next27: U18.8 (D3), U19.15 (Y3), U20.15 (Y3)
next28: U18.13 (D4), U19.14 (Y4), U20.14 (Y4)
next29: U18.14 (D5), U19.13 (Y5), U20.13 (Y5)
next30: U18.17 (D6), U19.12 (Y6), U20.12 (Y6)
next31: U18.18 (D7), U19.11 (Y7), U20.11 (Y7)
out0: J7.1, U2.18 (Y0)
out1: J7.2, U2.17 (Y1)
out2: J7.3, U2.16 (Y2)
out3: J7.4, U2.15 (Y3)
out4: J7.5, U2.14 (Y4)
out5: J7.6, U2.13 (Y5)
out6: J7.7, U2.12 (Y6)
out7: J7.8, U2.11 (Y7)
out8: J7.9, U7.18 (Y0)
out9: J7.10, U7.17 (Y1)
out10: J7.11, U7.16 (Y2)
out11: J7.12, U7.15 (Y3)
out12: J7.13, U7.14 (Y4)
out13: J7.14, U7.13 (Y5)
out14: J7.15, U7.12 (Y6)
out15: J7.16, U7.11 (Y7)
out16: J7.17, U12.18 (Y0)
out17: J7.18, U12.17 (Y1)
out18: J7.19, U12.16 (Y2)
out19: J7.20, U12.15 (Y3)
out20: J7.21, U12.14 (Y4)
out21: J7.22, U12.13 (Y5)
out22: J7.23, U12.12 (Y6)
out23: J7.24, U12.11 (Y7)
out24: J7.25, U16.18 (Y0)
out25: J7.26, U16.17 (Y1)
out26: J7.27, U16.16 (Y2)
out27: J7.28, U16.15 (Y3)
out28: J7.29, U16.14 (Y4)
out29: J7.30, U16.13 (Y5)
out30: J7.31, U16.12 (Y6)
out31: J7.32, U16.11 (Y7)
write: U4.19 (G2), U9.19 (G2), U14.19 (G2), U19.19 (G2)
~cwrite: J3.34, J8.34
~enable: U2.1 (G1), U7.1 (G1), U12.1 (G1), U16.1 (G1), U21.19 (P=R)
~read: J8.33, U2.19 (G2), U7.19 (G2), U12.19 (G2), U16.19 (G2)
~write: J2.34, U5.19 (G2), U10.19 (G2), U15.19 (G2), U20.19 (G2)
